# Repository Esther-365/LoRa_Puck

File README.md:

# LoRa_Puck
Building a LoRa project, based on the [HackClub LoRa Starter Project](https://blueprint.hackclub.com/starter-projects/lora#applying-these-concepts). I am using the [SX1262 by Semtech](https://www.semtech.com/products/wireless-rf/lora-connect/sx1262) for its radio module and [Microcontroller RP2040](https://pip-assets.raspberrypi.com/categories/814-rp2040/documents/RP-008371-DS-1-rp2040-datasheet.pdf). It's designed to send text from the Serial monitor over LoRa and a somewhat replica of it(one running the receiver firmware) can pick it up from a distance.

# How it works
The idea is pretty straightforward. I type a message into the Arduino Serial Monitor, and the RP2040 reads it. The RP2040 then sends the message as bytes to the SX1262 through SPI. The SX1262 takes those bytes, prepares them for LoRa transmission, and sends the signal through the antenna.

So, the RP2040 handles the instructions and the message, while the SX1262 handles the actual radio communication. The second LoRa device with matching radio settings would receive the message and turn the bytes back into readable text.

I plan to improve on this project and eventually create a mini RFID gate system, where an RFID card will act as the transmitter and send a signal to a LoRa receiver. The receiver will then determine whether access should be granted and instruct the gate to open or remain closed.

# Components
| Component | What it does |
|---|---|
| **RP2040** | The main microcontroller. It reads the message and communicates with the SX1262. |
| **SX1262** | The LoRa transceiver. It handles sending and receiving radio signals. |
| **W25Q128JV** | External flash memory used to store the RP2040's program. |
| **PE4259** | RF switch that connects the antenna to the transmit or receive path. |
| **FL1 (0900FM15K0039)** | Balun that connects the SX1262's differential RF pins to the single-ended RF path. |
| **Antenna** | Sends and receives the radio-frequency signal. |
| **USB-C** | Provides the USB connection for programming and serial communication. |
| **LED + 330 Ω resistor** | The LED is used as a transmission indicator, and the resistor limits the current flowing through it. |

# Firmware
I wrote the [firmware](lora_arduino.ino) using Arduino IDE, [RadioLib Library](https://github.com/jgromes/RadioLib/tree/master) for the SX1262 and [SPI library](https://github.com/arduino/ArduinoCore-avr/blob/master/libraries/SPI/src/SPI.h) to configure SPI communication.

You can find the full Bill of Materials [here](LoRa_BOM.xlsx).

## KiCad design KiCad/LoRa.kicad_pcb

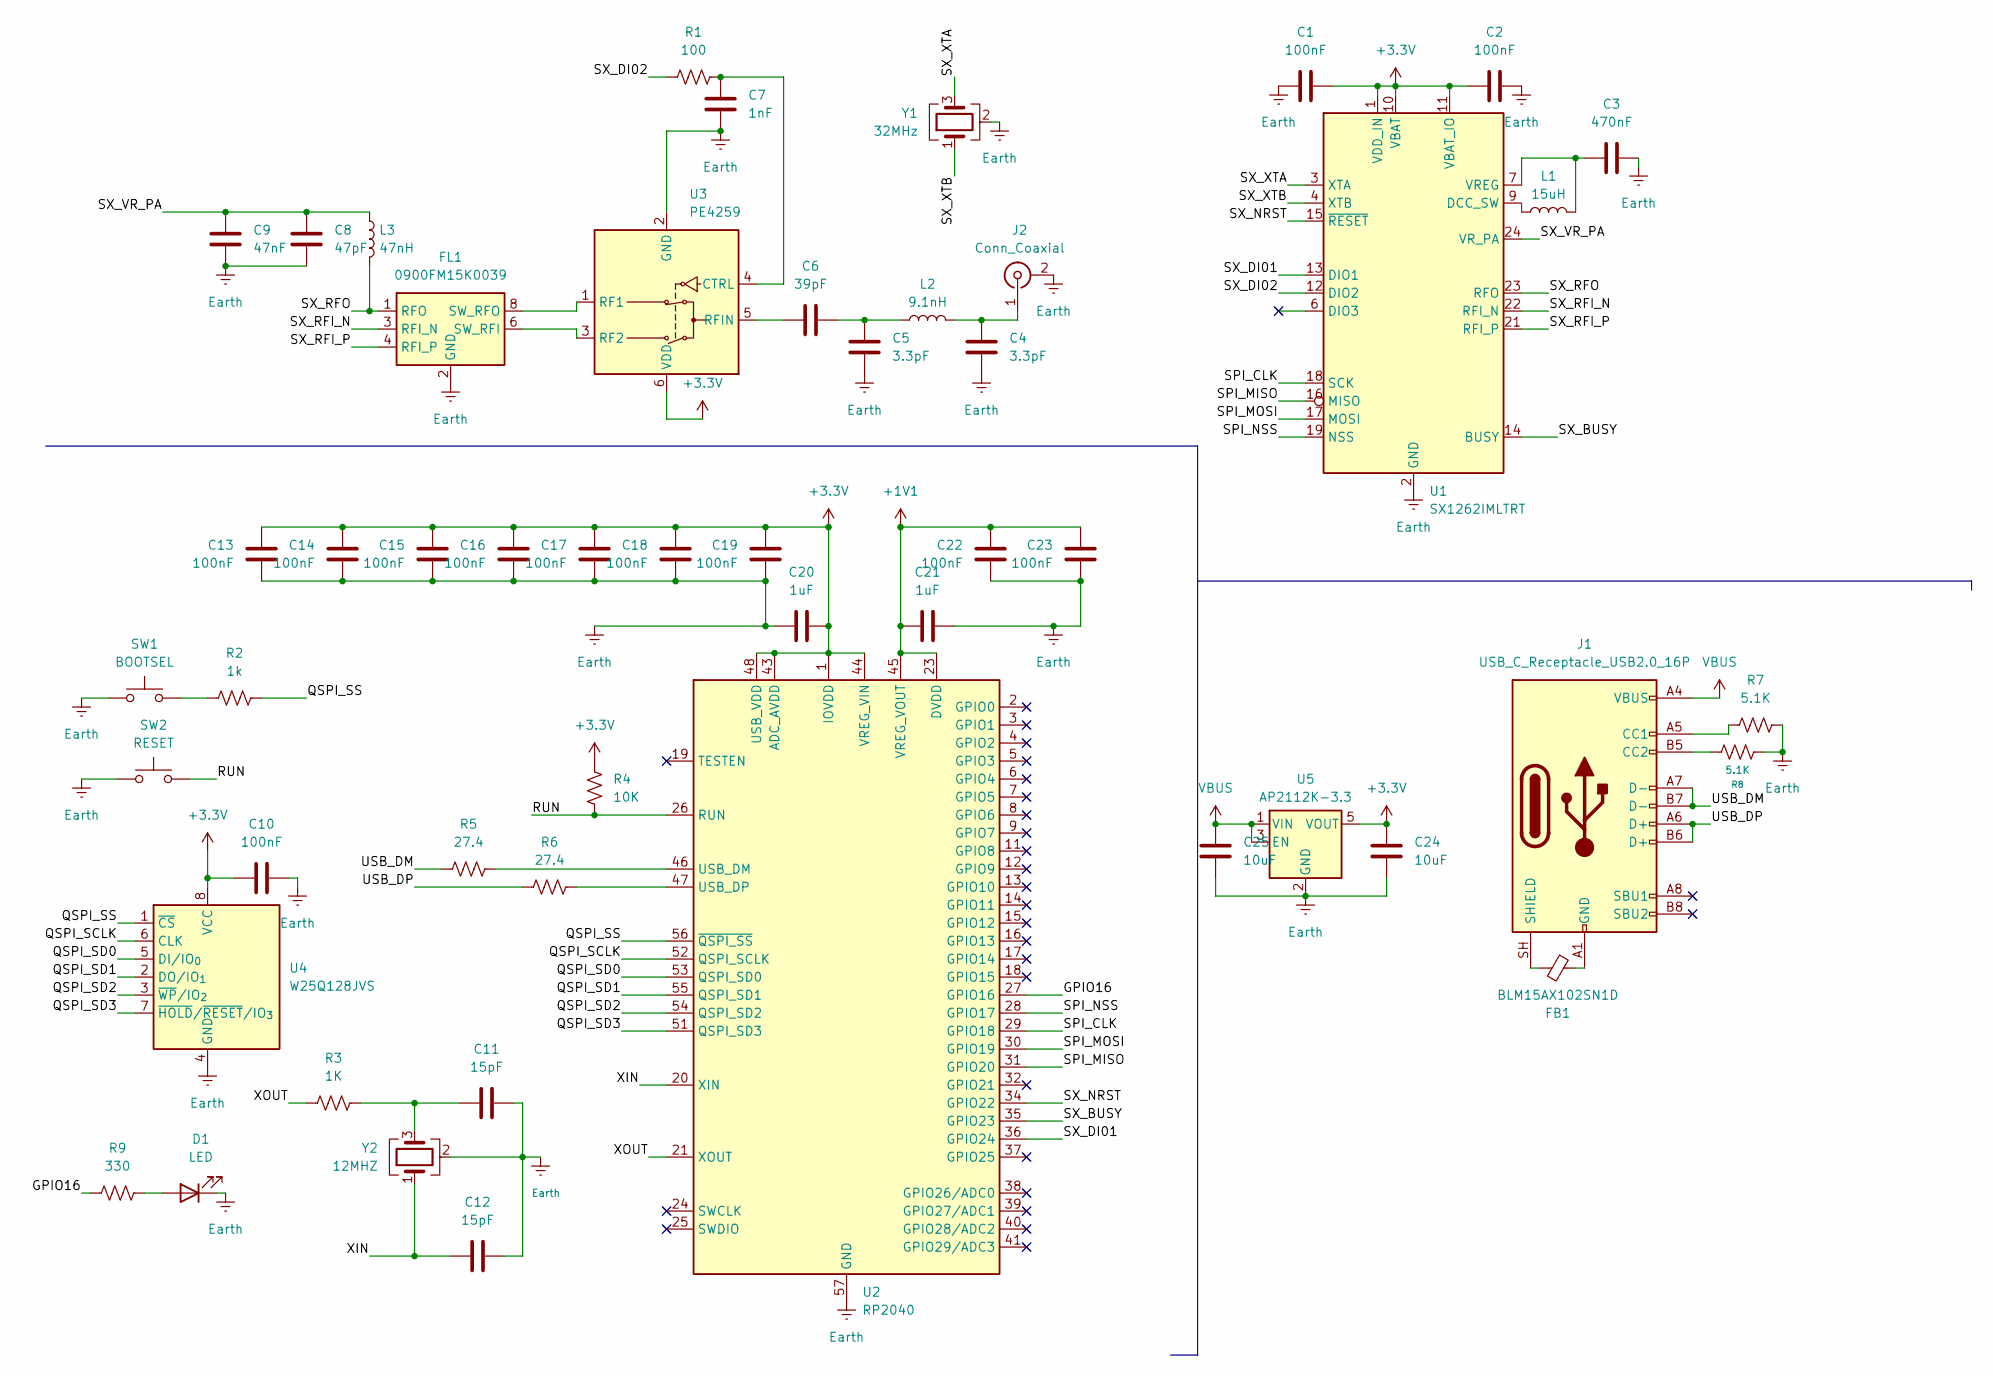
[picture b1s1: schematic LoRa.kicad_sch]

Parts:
C1, C2, C10, C13, C14, C15, C16, C17, C18, C19, C22, C23: 100nF; C_0402_1005Metric
C3: 470nF; C_0402_1005Metric
C4, C5: 3.3pF; C_0402_1005Metric
C6: 39pF; C_0402_1005Metric
C7: 1nF; C_0402_1005Metric
C8: 47pF; C_0402_1005Metric
C9: 47nF; C_0402_1005Metric
C11, C12: 15pF; C_0402_1005Metric
C20, C21: 1uF; C_0402_1005Metric
C24, C25: 10uF; C_0402_1005Metric
D1: LED; LED_D5.0mm
FB1: BLM15AX102SN1D; L_0402_1005Metric
FL1: 0900FM15K0039; Balun_Johanson_0900FM15K0039
J1: USB_C_Receptacle_USB2.0_16P; USB_C_Receptacle_GCT_USB4105-xx-A_16P_TopMnt_Horizontal
J2: Conn_Coaxial; U.FL_Hirose_U.FL-R-SMT-1_Vertical
L1: 15uH; L_0805_2012Metric
L2: 9.1nH; L_0402_1005Metric
L3: 47nH; L_0402_1005Metric
R1: 100; R_0402_1005Metric
R2: 1k; R_0402_1005Metric
R3: 1K; R_0402_1005Metric
R4: 10K; R_0402_1005Metric
R5, R6: 27.4; R_0402_1005Metric
R7, R8: 5.1K; R_0402_1005Metric
R9: 330; R_0402_1005Metric
SW1: BOOTSEL; SW_Tactile_SPST_NO_Straight_CK_PTS636Sx25SMTRLFS
SW2: RESET; SW_Tactile_SPST_NO_Straight_CK_PTS636Sx25SMTRLFS
U1: SX1262IMLTRT; QFN-24-1EP_4x4mm_P0.5mm_EP2.6x2.6mm
U2: RP2040; QFN-56-1EP_7x7mm_P0.4mm_EP3.2x3.2mm
U3: PE4259; SOT-363_SC-70-6
U4: W25Q128JVS; SOIC-8_5.3x5.3mm_P1.27mm
U5: AP2112K-3.3; SOT-23-5
Y1: 32MHz; Crystal_SMD_3225-4Pin_3.2x2.5mm
Y2: 12MHZ; Crystal_SMD_Abracon_ABM8G-4Pin_3.2x2.5mm

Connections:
+1V1: C21.2, C22.1, C23.1, U2.23 (DVDD), U2.45 (VREG_VOUT), U2.50 (DVDD)
+3.3V: C1.2, C2.1, C10.1, C13.1, C14.1, C15.1, C16.1, C17.1, C18.1, C19.1, C20.1, C24.1, R4.1, U1.1 (VDD_IN), U1.10 (VBAT), U1.11 (VBAT_IO), U2.1 (IOVDD), U2.10 (IOVDD), U2.22 (IOVDD), U2.33 (IOVDD), U2.42 (IOVDD), U2.43 (ADC_AVDD), U2.44 (VREG_VIN), U2.48 (USB_VDD), U2.49 (IOVDD), U3.6 (VDD), U4.8 (VCC), U5.5 (VOUT)
/GPIO16: R9.1, U2.27 (GPIO16)
/QSPI_SCLK: U2.52 (QSPI_SCLK), U4.6 (CLK)
/QSPI_SD0: U2.53 (QSPI_SD0), U4.5 (DI/IO_{0})
/QSPI_SD1: U2.55 (QSPI_SD1), U4.2 (DO/IO_{1})
/QSPI_SD2: U2.54 (QSPI_SD2), U4.3 (~WP/IO_{2})
/QSPI_SD3: U2.51 (QSPI_SD3), U4.7 (~HOLD/~RESET/IO_{3})
/QSPI_SS: R2.2, U2.56 (~QSPI_SS), U4.1 (~CS)
/RUN: R4.2, SW2.2, U2.26 (RUN)
/SPI_CLK: U1.18 (SCK), U2.29 (GPIO18)
/SPI_MISO: U1.16 (MISO), U2.31 (GPIO20)
/SPI_MOSI: U1.17 (MOSI), U2.30 (GPIO19)
/SPI_NSS: U1.19 (NSS), U2.28 (GPIO17)
/SX_BUSY: U1.14 (BUSY), U2.35 (GPIO23)
/SX_DI01: U1.13 (DIO1), U2.36 (GPIO24)
/SX_DI02: R1.1, U1.12 (DIO2)
/SX_NRST: U1.15 (~RESET), U2.34 (GPIO22)
/SX_RFI_N: FL1.3 (RFI_N), U1.22 (RFI_N)
/SX_RFI_P: FL1.4 (RFI_P), U1.21 (RFI_P)
/SX_RFO: FL1.1 (RFO), L3.2, U1.23 (RFO)
/SX_VR_PA: C8.1, C9.1, L3.1, U1.24 (VR_PA)
/SX_XTA: U1.3 (XTA), Y1.3
/SX_XTB: U1.4 (XTB), Y1.1
/USB_DM: J1.A7 (D-), J1.B7 (D-), R5.1
/USB_DP: J1.A6 (D+), J1.B6 (D+), R6.2
/XIN: C12.2, U2.20 (XIN), Y2.1
/XOUT: R3.1, U2.21 (XOUT)
Earth: C1.1, C2.2, C3.2, C4.2, C5.2, C7.2, C8.2, C9.2, C10.2, C11.2, C12.1, C13.2, C14.2, C15.2, C16.2, C17.2, C18.2, C19.2, C20.2, C21.1, C22.2, C23.2, C24.2, C25.2, D1.1 (K), FL1.2 (GND), FL1.5 (GND), FL1.7 (GND), FL1.9 (GND), FL1.10 (GND), J2.2 (Ext), R7.2, R8.2, SW1.1, SW2.1, U1.2 (GND), U1.5 (GND), U1.8 (GND), U1.20 (GND), U1.25 (GND), U2.57 (GND), U3.2 (GND), U4.4 (GND), U5.2 (GND), Y1.2 (G), Y1.4 (G), Y2.2 (G), Y2.4 (G)
unnamed: C5.1, C6.2, L2.1
unnamed: C11.1, R3.2, Y2.3
unnamed: D1.2 (A), R9.2
unnamed: FB1.1, J1.A1 (GND), J1.A12 (GND), J1.B1 (GND), J1.B12 (GND)
unnamed: FL1.6 (SW_RFI), U3.3 (RF2)
unnamed: FL1.8 (SW_RFO), U3.1 (RF1)
unnamed: J1.A5 (CC1), R7.1
unnamed: J1.B5 (CC2), R8.1
unnamed: FB1.2, J1.SH (SHIELD)
unnamed: C4.1, J2.1 (In), L2.2
unnamed: R2.1, SW1.2
unnamed: L1.1, U1.9 (DCC_SW)
unnamed: C3.1, L1.2, U1.7 (VREG)
unnamed: R5.2, U2.46 (USB_DM)
unnamed: R6.1, U2.47 (USB_DP)
unnamed: C7.1, R1.2, U3.4 (CTRL)
unnamed: C6.1, U3.5 (RFIN)
VBUS: C25.1, J1.A4 (VBUS), J1.A9 (VBUS), J1.B4 (VBUS), J1.B9 (VBUS), U5.1 (VIN), U5.3 (EN)

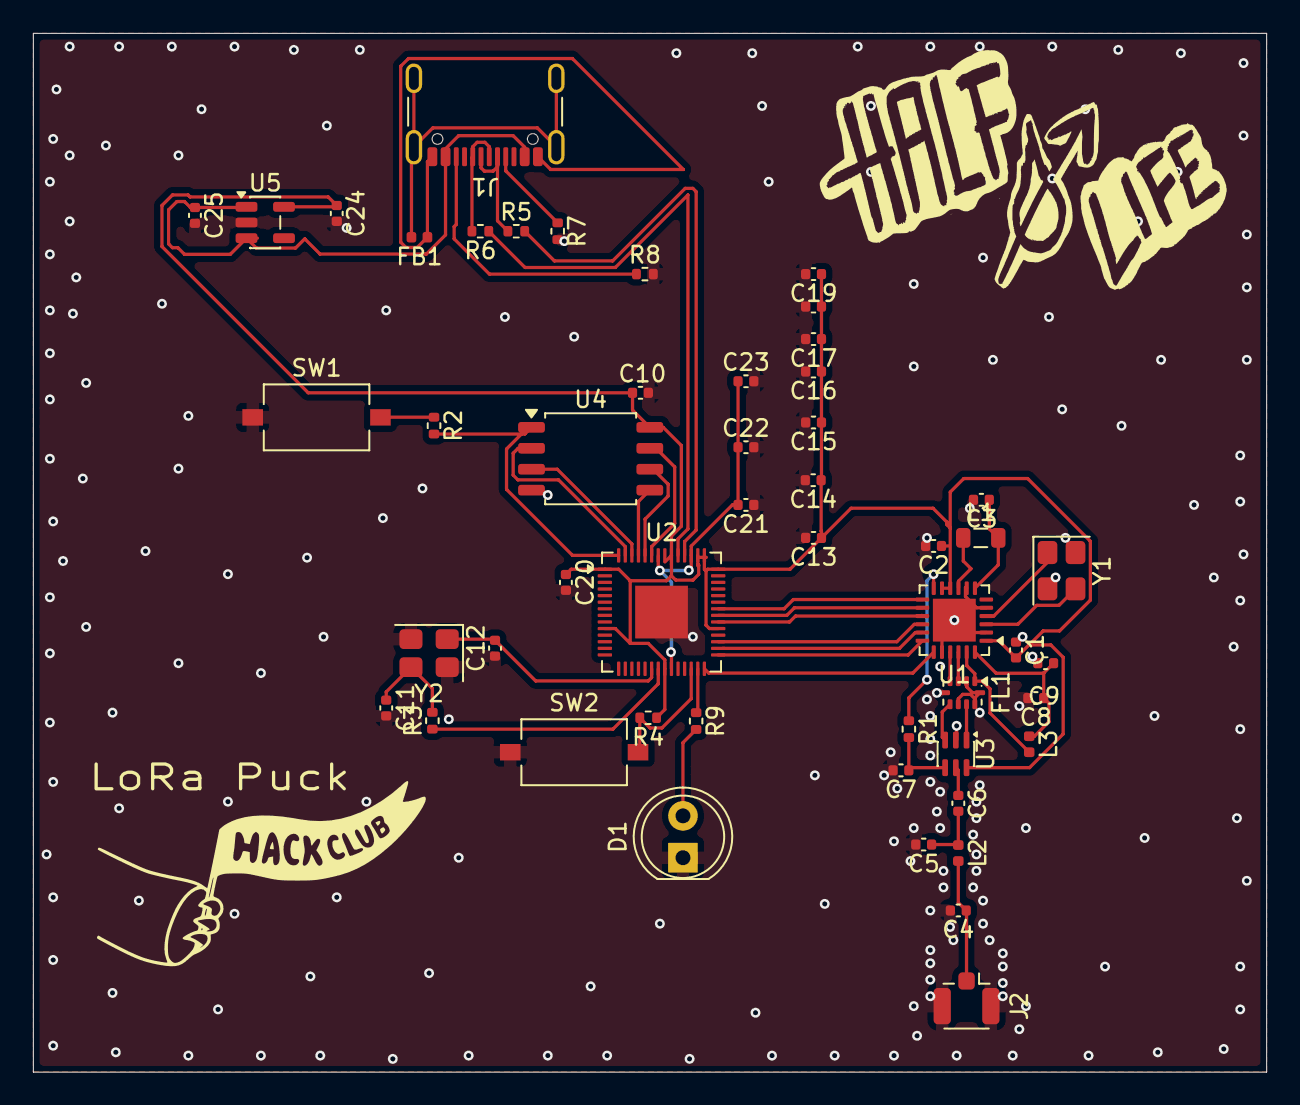
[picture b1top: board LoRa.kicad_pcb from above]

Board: 4 copper layers, 74.8 x 63.0 mm, 51 parts (0 on the bottom side), 47 nets.

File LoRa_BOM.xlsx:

Part | Qty | Unit ($) | Total ($) | Vendor
U.FL Connector | 1 | 1.67 | 1.67 | DigiKey
Antenna | 1 | 9.99 | 9.99 | Amazon
100nF capacitor | 20 | 0.1 | 2 | DigiKey
470NF Capacitor | 2 | 0.28999999999999998 | 0.57999999999999996 | DigiKey
3.3pF capacitor | 4 | 0.02 | 0.08 | DigiKey
39pF capacitor | 2 | 0.04 | 0.08 | DigiKey
1nF | 2 | 0.09 | 0.18 | DigiKey
47pFCapacitor | 3 | 0.04 | 0.12 | DigiKey
47nF Capacitor | 2 | 0.09 | 0.18 | DigiKey
15pF | 4 | 0.03 | 0.12 | DigiKey
1uF | 4 | 0.5 | 2 | Mouser
10uF Capacitor | 5 | 0.1 | 0.5 | DigiKey
LED | 2 | 0.3 | 0.6 | DigiKey
BLM15AX102SN1D | 3 | 0.1 | 0.30000000000000004 | DigiKey
0900FM15K0039 | 2 | 0.5 | 1 | DigiKey
USBC Receptacle | 1 | 0.8 | 0.8 | DigiKey
15uH inductor | 3 | 0.1 | 0.30000000000000004 | DigiKey
9.1nH inductor | 3 | 0.2 | 0.60000000000000009 | DigiKey
47nH inductor | 3 | 0.2 | 0.60000000000000009 | DigiKey
100 ohms Resistor | 3 | 0.04 | 0.12 | DigiKey
1K Resistor | 3 | 0.03 | 0.09 | DigiKey
10K Resistor | 3 | 0.02 | 0.06 | DigiKey
27.4 Resistor | 6 | 0.05 | 0.30000000000000004 | DigiKey
5.1k resistor | 6 | 0.3 | 1.7999999999999998 | DigiKey
330 Resistor | 2 | 0.03 | 0.06 | DigiKey
SX1262IMLTRT | 1 | 9.3000000000000007 | 9.3000000000000007 | Amazon
RP2040 | 2 | 0.8 | 1.6 | DigiKey
PE4259 | 2 | 1.2 | 2.4 | LCSC
W25Q128JVS | 1 | 5.8 | 5.8 | DigiKey
AP2112K-3.3 | 2 | 0.28000000000000003 | 0.56000000000000005 | DigiKey
32MHz Crystal | 2 | 0.54 | 1.08 | DigiKey
PCB | 1 | 8 | 8 | JLCPCB
12MHz Crystal | 2 | 0.7 | 1.4 | DigiKey
Switches | 4 | 0.28999999999999998 | 1.1599999999999999 | DigiKey
Total | 107 |  | 55.43
Source: transcribed from the user's BOM screenshots; items that appeared in two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
